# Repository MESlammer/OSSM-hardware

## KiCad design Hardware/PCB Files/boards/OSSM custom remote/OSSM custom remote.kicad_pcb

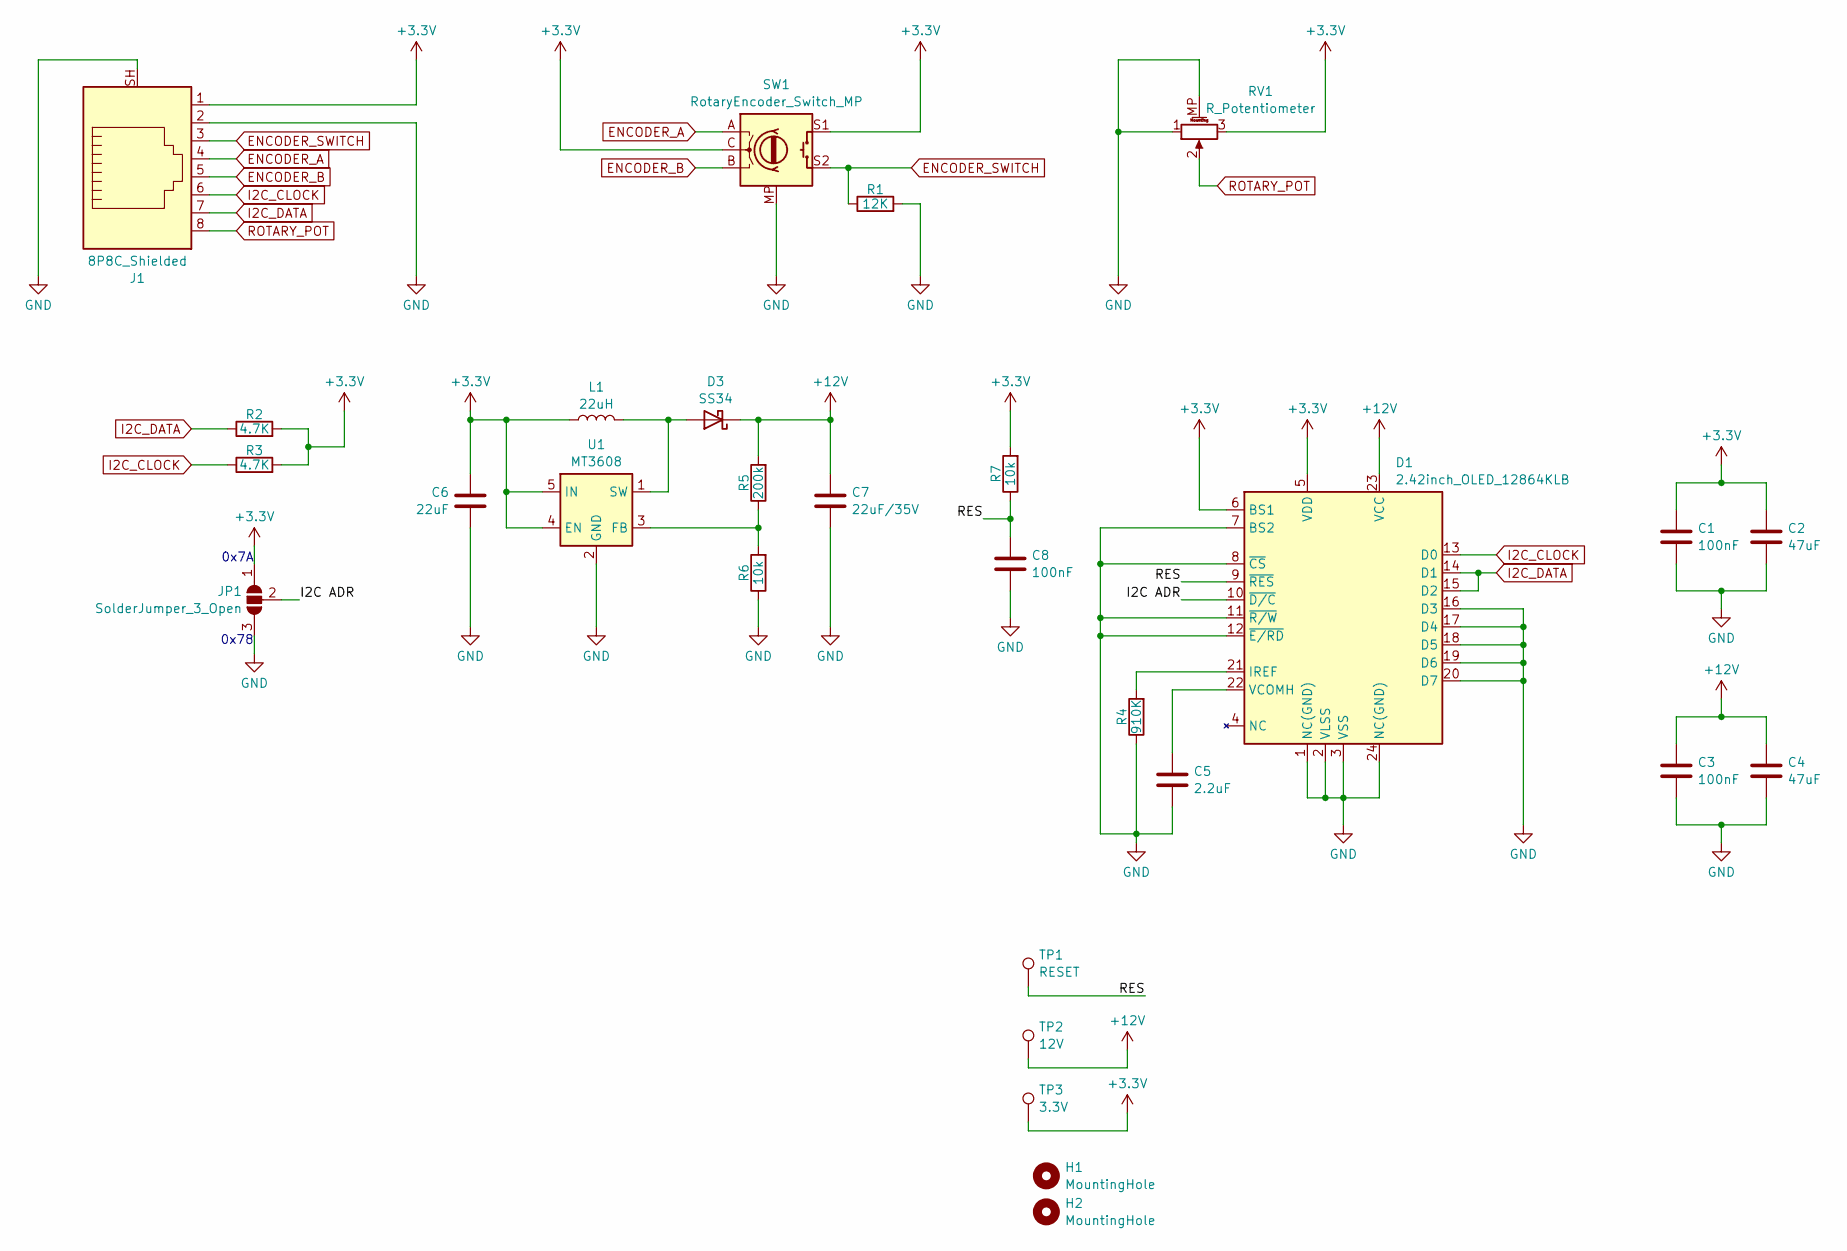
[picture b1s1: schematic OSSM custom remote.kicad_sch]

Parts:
C1, C3, C8: 100nF; C_0805_2012Metric
C2, C4: 47uF; C_0805_2012Metric
C5: 2.2uF; C_0805_2012Metric
C6: 22uF; C_0805_2012Metric
C7: 22uF/35V; C_0805_2012Metric
D1: 2.42inch_OLED_12864KLB; 2.42_OLED_24P_FPC_0.5MM
D3: SS34; D_SMA
H1, H2: MountingHole; MountingHole_3.2mm_M3_DIN965_Pad
J1: 8P8C_Shielded; RJ45_Molex_438605025_Horizontal; MPN 43860-5025
JP1: SolderJumper_3_Open; SolderJumper-3_P1.3mm_Open_RoundedPad1.0x1.5mm_NumberLabels
L1: 22uH; L_1812_4532Metric; MPN LQH43MN220K
R1: 12K; R_0805_2012Metric
R2, R3: 4.7K; R_0805_2012Metric
R4: 910K; R_0805_2012Metric
R5: 200k; R_0805_2012Metric
R6, R7: 10k; R_0805_2012Metric
RV1: R_Potentiometer; Potentiometer_Alps_RK09L_Single_Vertical; MPN RK09L1140A2U
SW1: RotaryEncoder_Switch_MP; RotaryEncoder_Alps_EC11E-Switch_Vertical_H20mm; MPN EC11E15244G1
TP1: RESET; TestPoint_Pad_D1.5mm
TP2: 12V; TestPoint_Pad_D1.5mm
TP3: 3.3V; TestPoint_Pad_D1.5mm
U1: MT3608; SOT-23-6; MPN MT3608

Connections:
+3.3V: C1.1, C2.1, C6.1, D1.5 (VDD), D1.6 (BS1), J1.1, JP1.1 (A), L1.1, R2.2, R3.2, R7.2, RV1.3, SW1.C, SW1.S1, TP3.1, U1.4 (EN), U1.5 (IN)
+12V: C3.1, C4.1, C7.1, D1.23 (VCC), D3.1 (K), R5.2, TP2.1
/I2C ADR: D1.10 (~D/C), JP1.2 (C)
/RES: C8.1, D1.9 (~RES), R7.1, TP1.1
ENCODER_A: J1.4, SW1.A
ENCODER_B: J1.5, SW1.B
ENCODER_SWITCH: J1.3, R1.1, SW1.S2
GND: C1.2, C2.2, C3.2, C4.2, C5.2, C6.2, C7.2, C8.2, D1.1 (NC(GND)), D1.2 (VLSS), D1.3 (VSS), D1.7 (BS2), D1.8 (~CS), D1.11 (~R/W), D1.12 (~E/RD), D1.16 (D3), D1.17 (D4), D1.18 (D5), D1.19 (D6), D1.20 (D7), D1.24 (NC(GND)), J1.2, J1.SH, JP1.3 (B), R1.2, R4.1, R6.1, RV1.1, RV1.MP (MountPin), SW1.MP, U1.2 (GND)
I2C_CLOCK: D1.13 (D0), J1.6, R3.1
I2C_DATA: D1.14 (D1), D1.15 (D2), J1.7, R2.1
unnamed: D1.21 (IREF), R4.2
unnamed: C5.1, D1.22 (VCOMH)
unnamed: D3.2 (A), L1.2, U1.1 (SW)
unnamed: R5.1, R6.2, U1.3 (FB)
ROTARY_POT: J1.8, RV1.2

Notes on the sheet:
0x7A
0x78

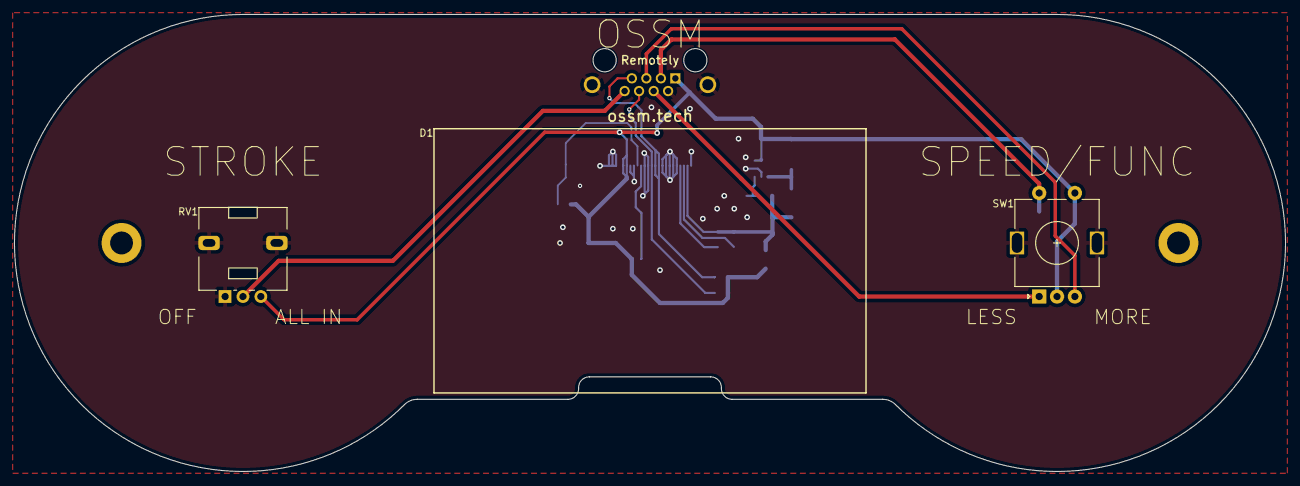
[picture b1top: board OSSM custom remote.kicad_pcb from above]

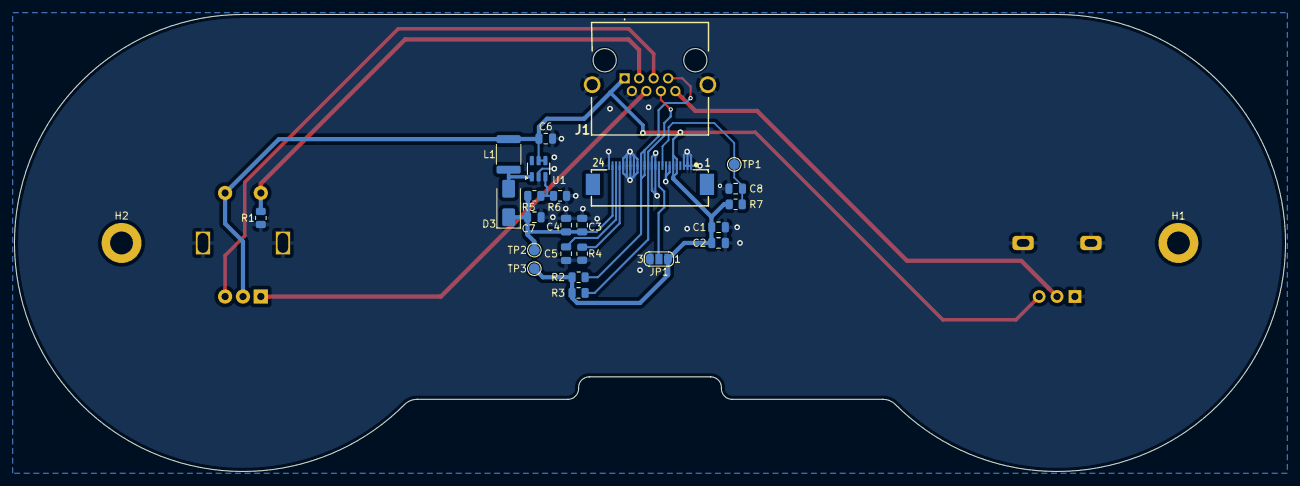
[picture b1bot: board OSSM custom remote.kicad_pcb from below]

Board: 2 copper layers, 178.0 x 64.0 mm, 28 parts (25 on the bottom side), 15 nets.

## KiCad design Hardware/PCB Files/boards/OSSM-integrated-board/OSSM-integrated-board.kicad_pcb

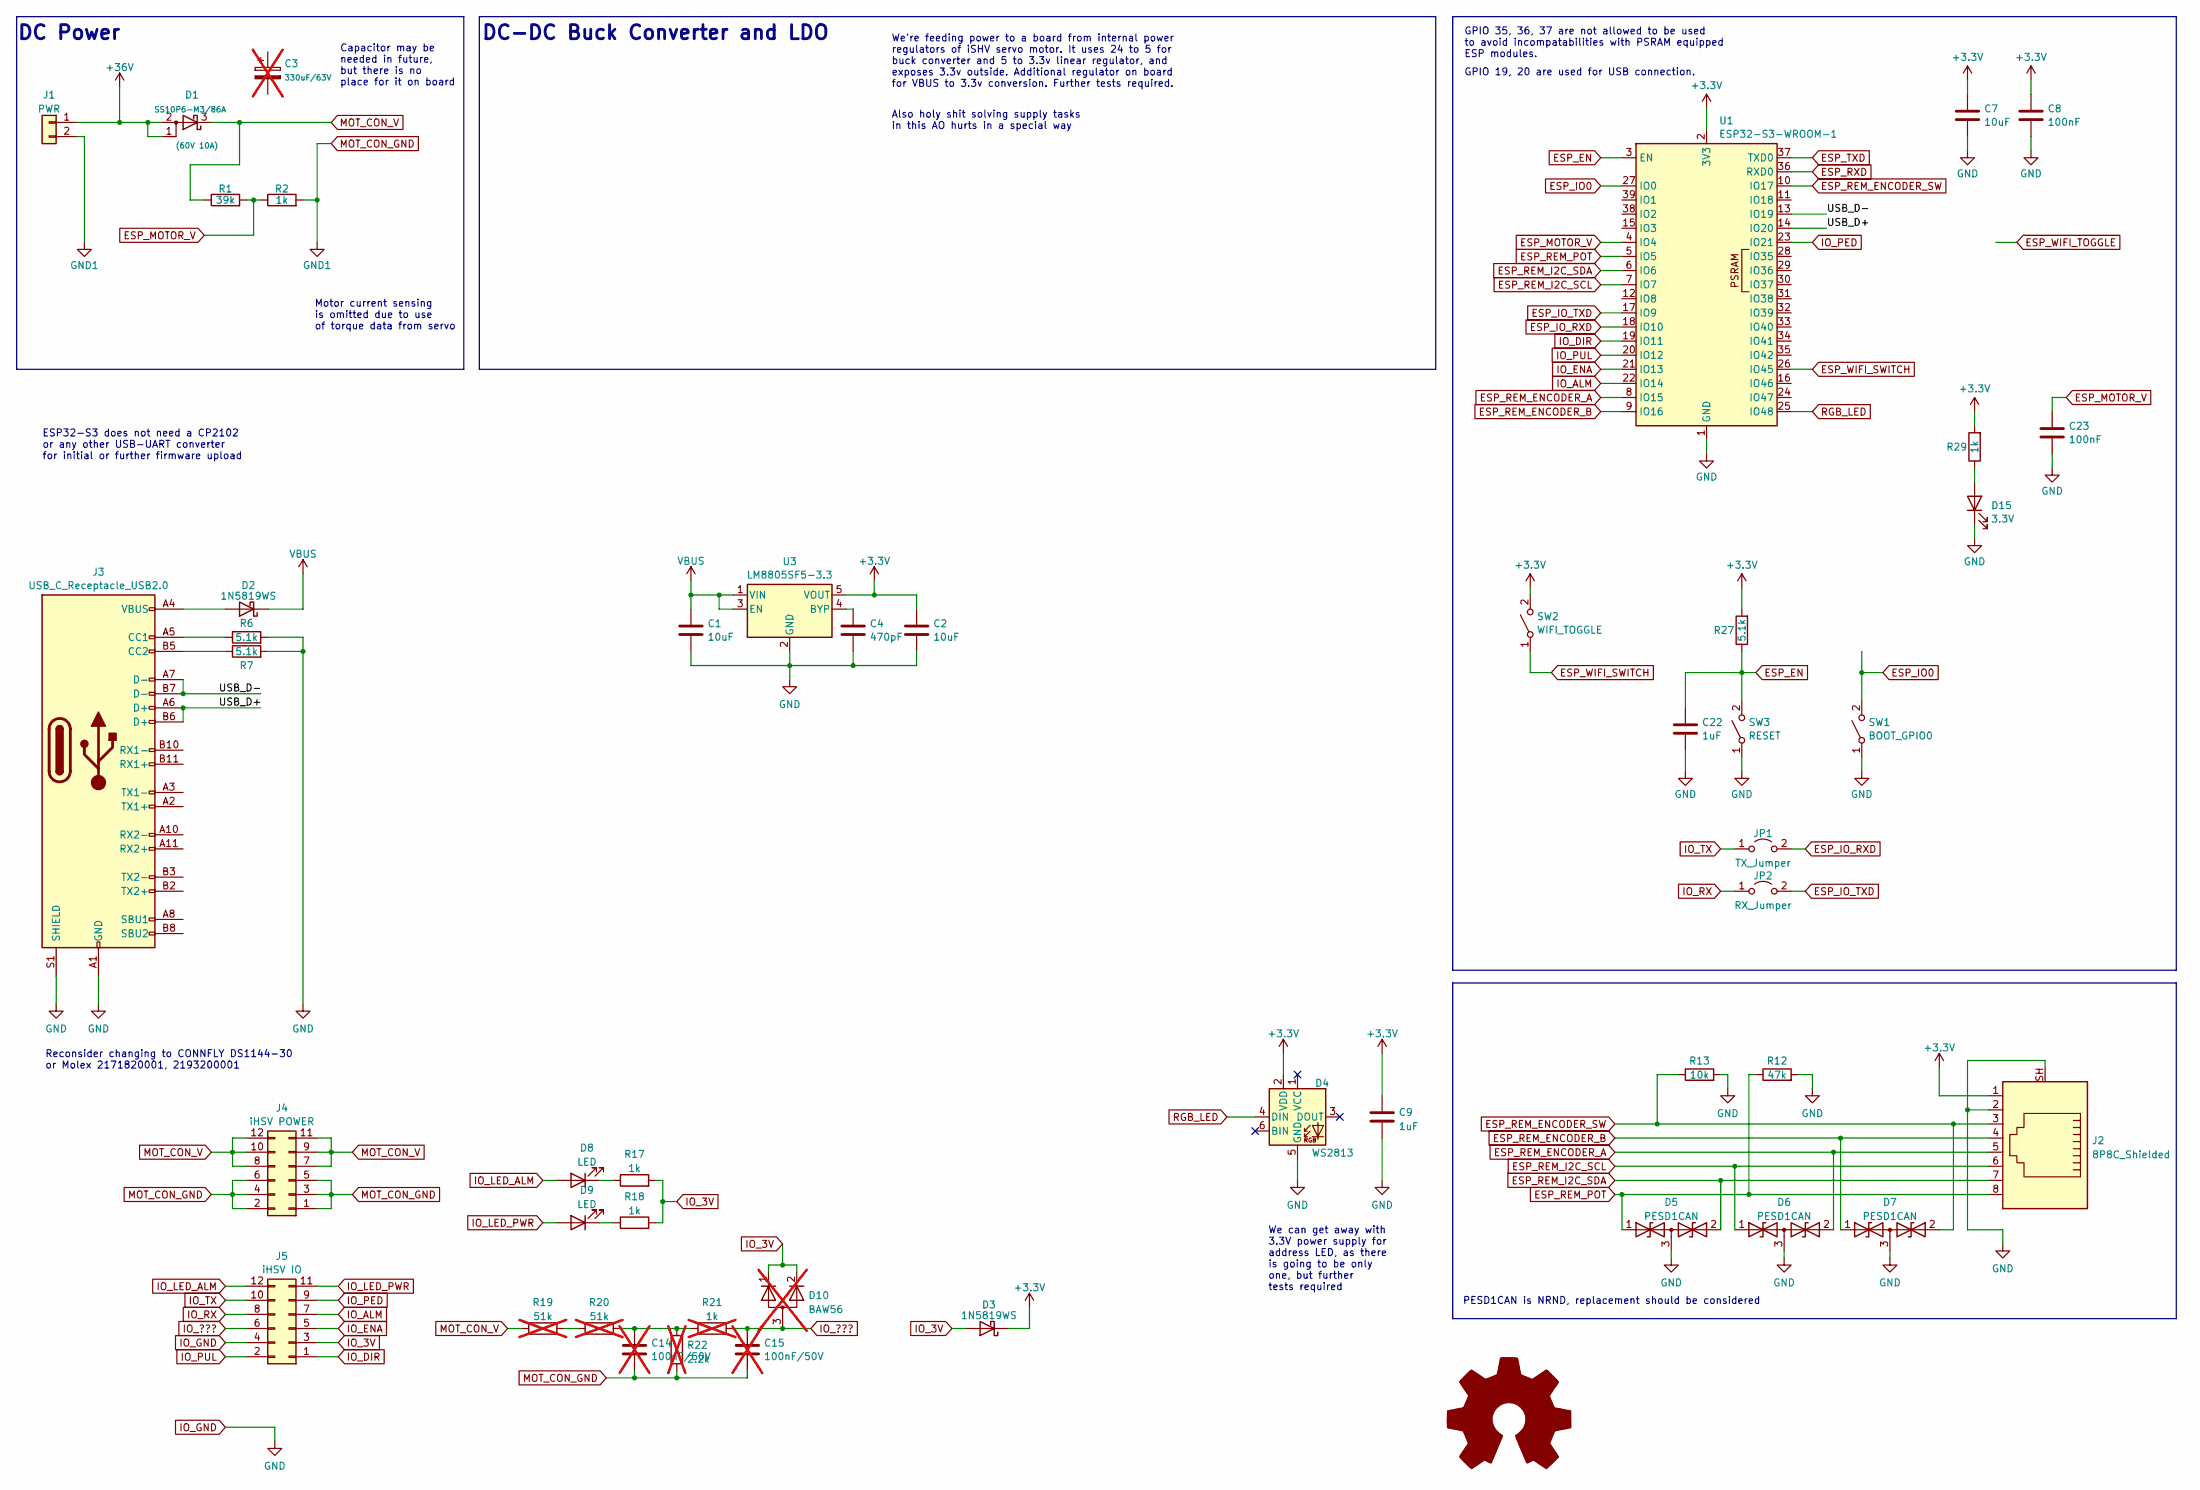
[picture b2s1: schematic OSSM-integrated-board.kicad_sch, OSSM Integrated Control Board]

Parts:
C1, C2, C7: 10uF; C_0402_1005Metric
C3: 330uF/63V; not fitted
C4: 470pF; C_0402_1005Metric
C8, C23: 100nF; C_0402_1005Metric
C9, C22: 1uF; C_0402_1005Metric
C14, C15: 100nF/50V; C_0805_2012Metric; not fitted
D1: SS10P6-M3/86A; TO-277A
D2, D3: 1N5819WS; D_SOD-323
D4: WS2813; LED_WS2812_PLCC6_5.0x5.0mm_P1.6mm
D5, D6, D7: PESD1CAN; SOT-23
D8, D9: LED; LED_0805_2012Metric
D10: BAW56; SOT-23-3; not fitted
D15: 3.3V; LED_0805_2012Metric
J1: PWR; Molex_Micro-Fit_3.0_43045-0212_2x01_P3.00mm_Vertical
J2: 8P8C_Shielded; RJ45_TE_1-338088-3_Vertical_Top_Entry
J3: USB_C_Receptacle_USB2.0; USB_C_Receptacle_Molex_204711-0001
J4: iHSV POWER; PinHeader_2x06_P2.00mm_Horizontal
J5: iHSV IO; PinHeader_2x06_P2.00mm_Horizontal
JP1: TX_Jumper; SolderJumper-2_P1.3mm_Open_TrianglePad1.0x1.5mm
JP2: RX_Jumper; SolderJumper-2_P1.3mm_Open_TrianglePad1.0x1.5mm
R1: 39k; R_0805_2012Metric
R2: 1k; R_0805_2012Metric
R6, R7, R27: 5.1k; R_0402_1005Metric
R12: 47k; R_0402_1005Metric
R13: 10k; R_0402_1005Metric
R17, R18, R29: 1k; R_0402_1005Metric
R19, R20: 51k; R_0402_1005Metric; not fitted
R21: 1k; R_0402_1005Metric; not fitted
R22: 2.2k; R_0402_1005Metric; not fitted
SW1: BOOT_GPIO0; SW_SPST_HRO_K2-1107ST
SW2: WIFI_TOGGLE; SW_SPST_HRO_K2-1107ST
SW3: RESET; SW_SPST_HRO_K2-1107ST
U1: ESP32-S3-WROOM-1
U3: LM8805SF5-3.3; SOT-23-5

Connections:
+3.3V: C2.1, C7.1, C8.1, C9.2, D3.1 (K), D4.2 (VDD), J2.1, R27.2, R29.2, SW2.2 (B), U1.2 (3V3), U3.5 (VOUT)
+36V: D1.1 (A), D1.2 (A), J1.1
/USB_D+: J3.A6 (D+), J3.B6 (D+), U1.14 (IO20)
/USB_D-: J3.A7 (D-), J3.B7 (D-), U1.13 (IO19)
ESP_EN: C22.1, R27.1, SW3.2 (B), U1.3 (EN)
ESP_IO0: SW1.2 (B), U1.27 (IO0)
ESP_IO_RXD: JP1.2 (B), U1.18 (IO10)
ESP_IO_TXD: JP2.2 (B), U1.17 (IO9)
ESP_MOTOR_V: C23.1, R1.2, R2.1, U1.4 (IO4)
ESP_REM_ENCODER_A: D6.2 (A2), J2.5, U1.8 (IO15)
ESP_REM_ENCODER_B: D7.1 (A1), J2.4, U1.9 (IO16)
ESP_REM_ENCODER_SW: D7.2 (A2), J2.3, R13.1, U1.10 (IO17)
ESP_REM_I2C_SCL: D6.1 (A1), J2.6, U1.7 (IO7)
ESP_REM_I2C_SDA: D5.2 (A2), J2.7, U1.6 (IO6)
ESP_REM_POT: D5.1 (A1), J2.8, R12.1, U1.5 (IO5)
ESP_RXD: U1.36 (RXD0)
ESP_TXD: U1.37 (TXD0)
ESP_WIFI_SWITCH: SW2.1 (A), U1.26 (IO45)
IO_3V: D3.2 (A), D10.1 (K), D10.2 (K), J5.3, R17.2, R18.2
IO_???: C15.2, D10.3 (A), J5.6, R21.2
IO_ALM: J5.7, U1.22 (IO14)
IO_DIR: J5.1, U1.19 (IO11)
IO_ENA: J5.5, U1.21 (IO13)
IO_GND: C1.2, C2.2, C4.2, C7.2, C8.2, C9.1, C22.2, C23.2, D4.5 (GND), D5.3 (common), D6.3 (common), D7.3 (common), D15.1 (K), J2.2, J2.SH, J3.A1 (GND), J3.A12 (GND), J3.B1 (GND), J3.B12 (GND), J3.S1 (SHIELD), J5.4, R6.2, R7.2, R12.2, R13.2, SW1.1 (A), SW3.1 (A), U1.1 (GND), U1.40 (GND), U1.41 (GND), U3.2 (GND)
IO_LED_ALM: D8.2 (A), J5.12
IO_LED_PWR: D9.2 (A), J5.11
IO_PED: J5.9, U1.23 (IO21)
IO_PUL: J5.2, U1.20 (IO12)
IO_RX: J5.8, JP2.1 (A)
IO_TX: J5.10, JP1.1 (A)
MOT_CON_GND: C14.2, C15.1, J1.2, J4.1, J4.2, J4.3, J4.4, J4.5, J4.6, R2.2, R22.2
MOT_CON_V: D1.3 (K), J4.7, J4.8, J4.9, J4.10, J4.11, J4.12, R1.1, R19.1
unnamed: C14.1, R20.2, R21.1, R22.1
unnamed: D2.2 (A), J3.A4 (VBUS), J3.A9 (VBUS), J3.B4 (VBUS), J3.B9 (VBUS)
unnamed: D8.1 (K), R17.1
unnamed: D9.1 (K), R18.1
unnamed: D15.2 (A), R29.1
unnamed: J3.A5 (CC1), R6.1
unnamed: J3.B5 (CC2), R7.1
unnamed: R19.2, R20.1
unnamed: C4.1, U3.4 (BYP)
RGB_LED: D4.4 (DIN), U1.25 (IO48)
VBUS: C1.1, D2.1 (K), U3.1 (VIN), U3.3 (EN)

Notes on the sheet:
GPIO 19, 20 are used for USB connection.
We're feeding power to a board from internal power regulators of iSHV servo motor. It uses 24 to 5 for buck converter and 5 to 3.3v linear regulator, and exposes 3.3v outside. Additional regulator on board for VBUS to 3.3v conversion. Further tests required.
Motor current sensing is omitted due to use of torque data from servo
We can get away with 3.3V power supply for address LED, as there is going to be only one, but further tests required
Capacitor may be needed in future, but there is no place for it on board
PESD1CAN is NRND, replacement should be considered
Reconsider changing to CONNFLY DS1144-30 or Molex 2171820001, 2193200001
DC-DC Buck Converter and LDO
GPIO 35, 36, 37 are not allowed to be used to avoid incompatabilities with PSRAM equipped ESP modules.
DC Power
ESP32-S3 does not need a CP2102 or any other USB-UART converter for initial or further firmware upload
Also holy shit solving supply tasks in this AO hurts in a special way

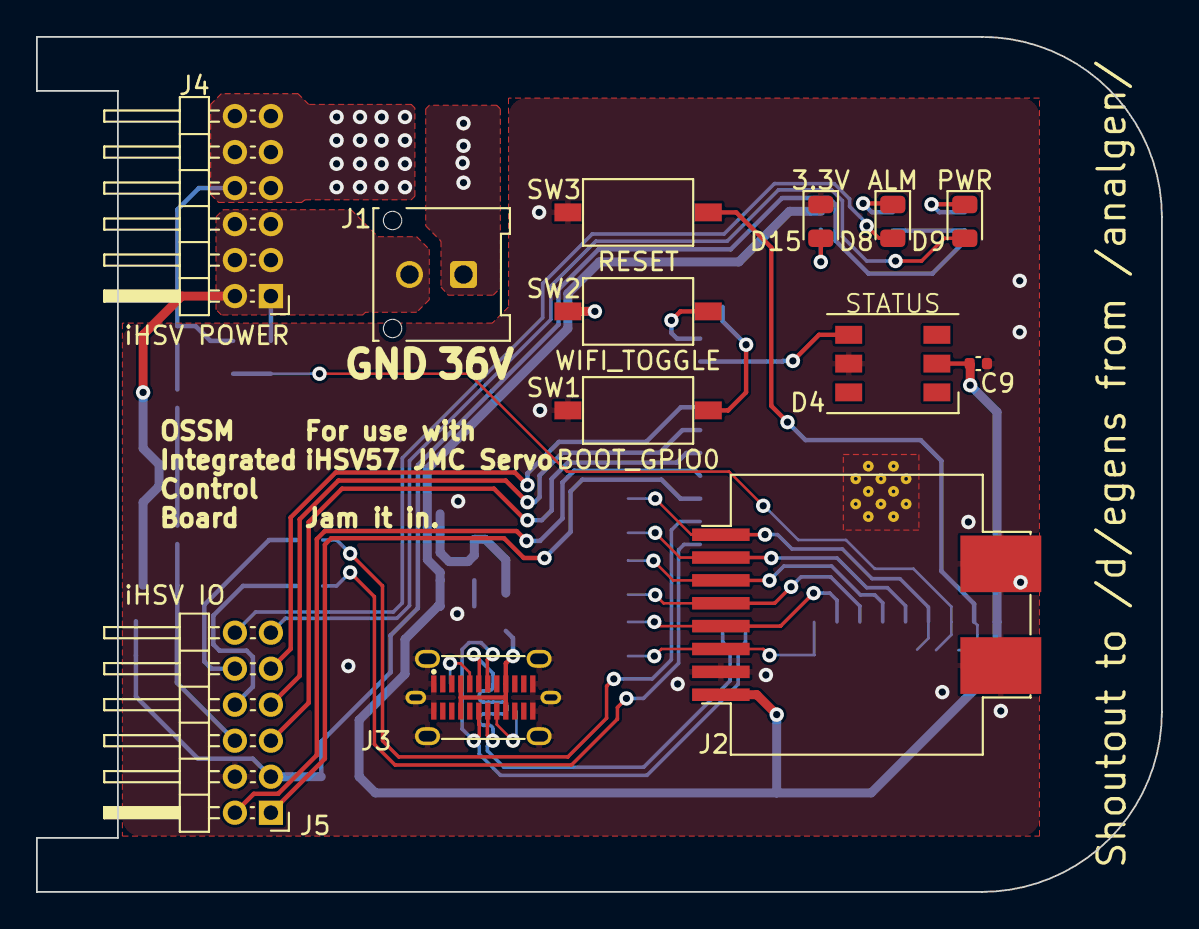
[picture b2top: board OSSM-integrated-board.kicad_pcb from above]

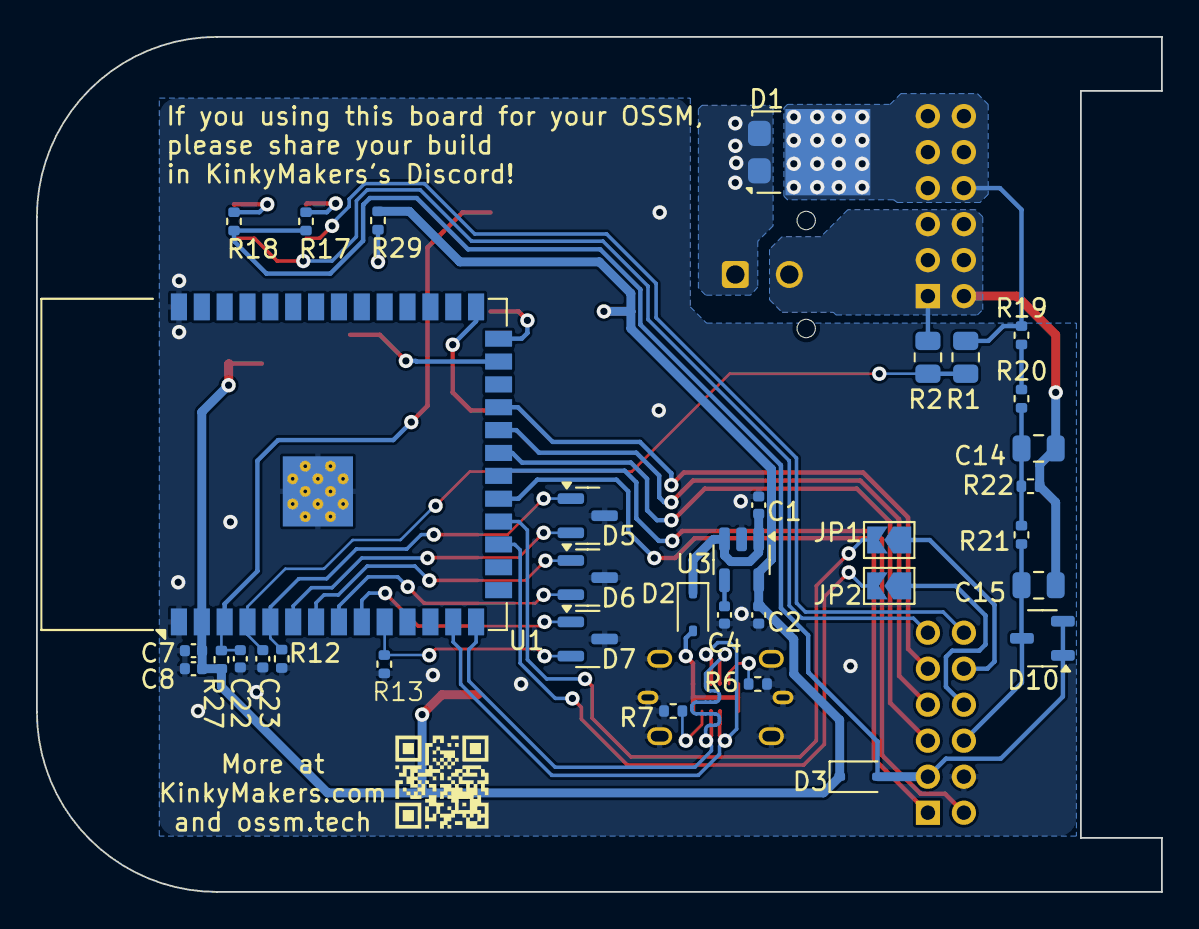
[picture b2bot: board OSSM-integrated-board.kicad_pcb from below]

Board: 2 copper layers, 62.5 x 47.5 mm, 47 parts (34 on the bottom side), 41 nets.

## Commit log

2024-06-12 draft of modbus support
2024-08-25 Changes for OSSM ICB
2024-10-29 Mote changes for OSSM ICB
2024-11-02 Removing hardware files and adding ICB sources
2024-11-04 Prettify partition.csv
